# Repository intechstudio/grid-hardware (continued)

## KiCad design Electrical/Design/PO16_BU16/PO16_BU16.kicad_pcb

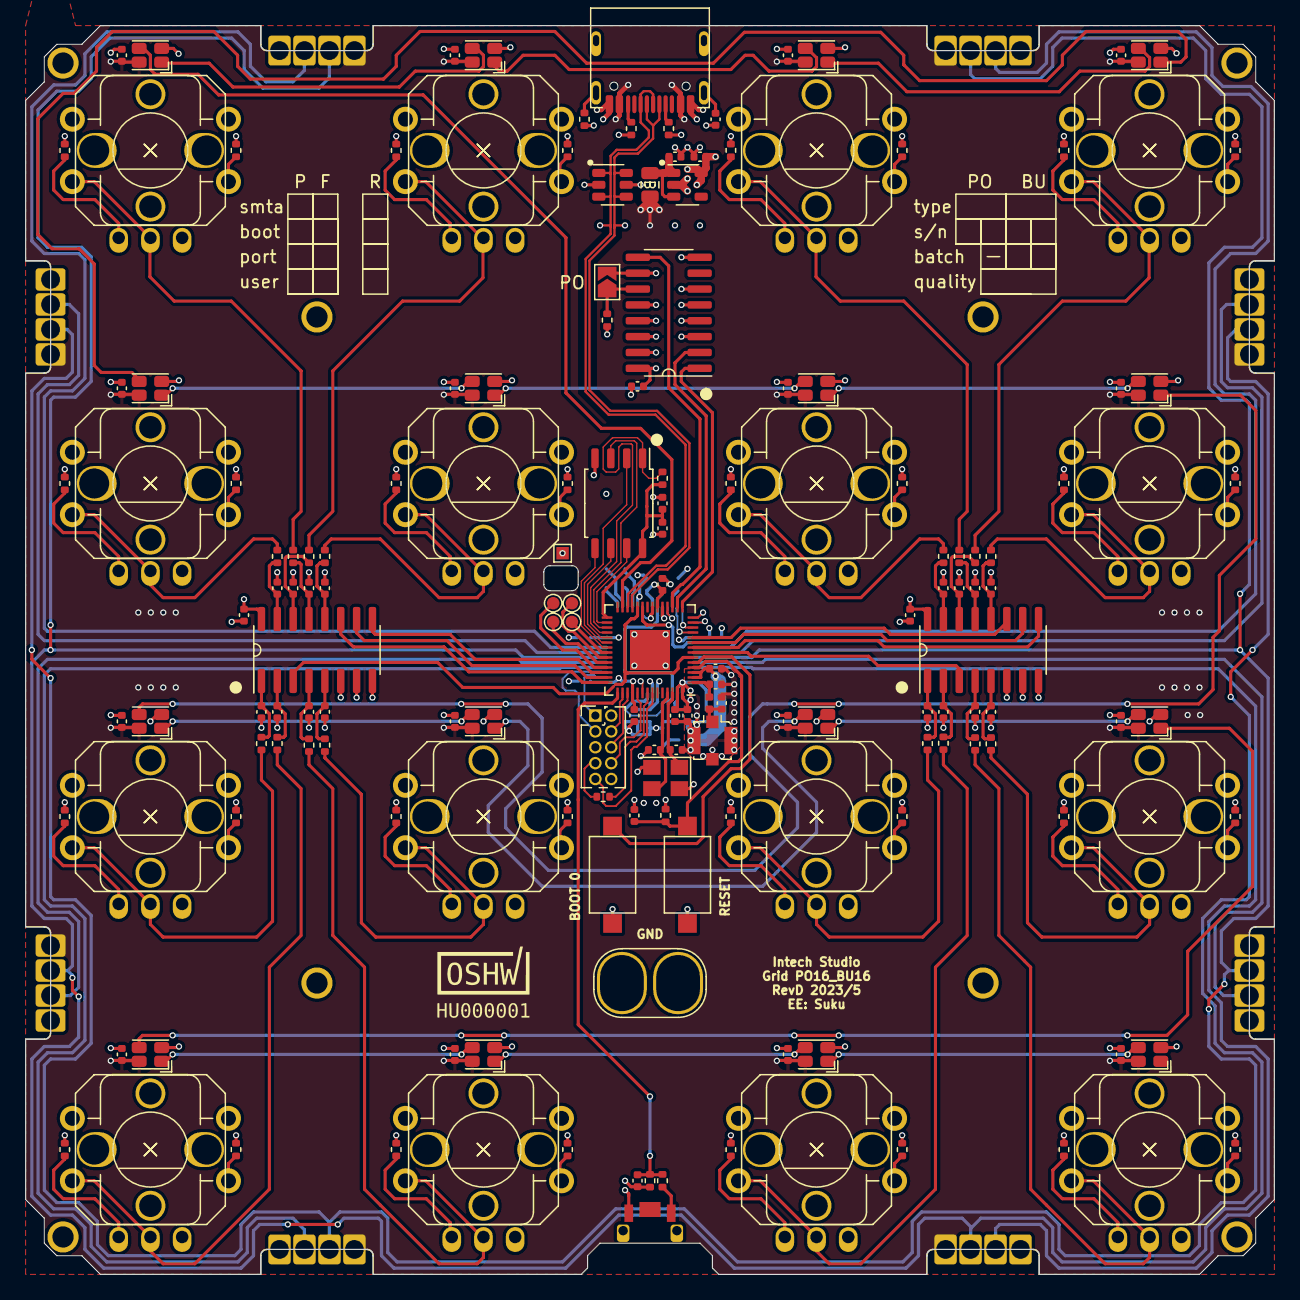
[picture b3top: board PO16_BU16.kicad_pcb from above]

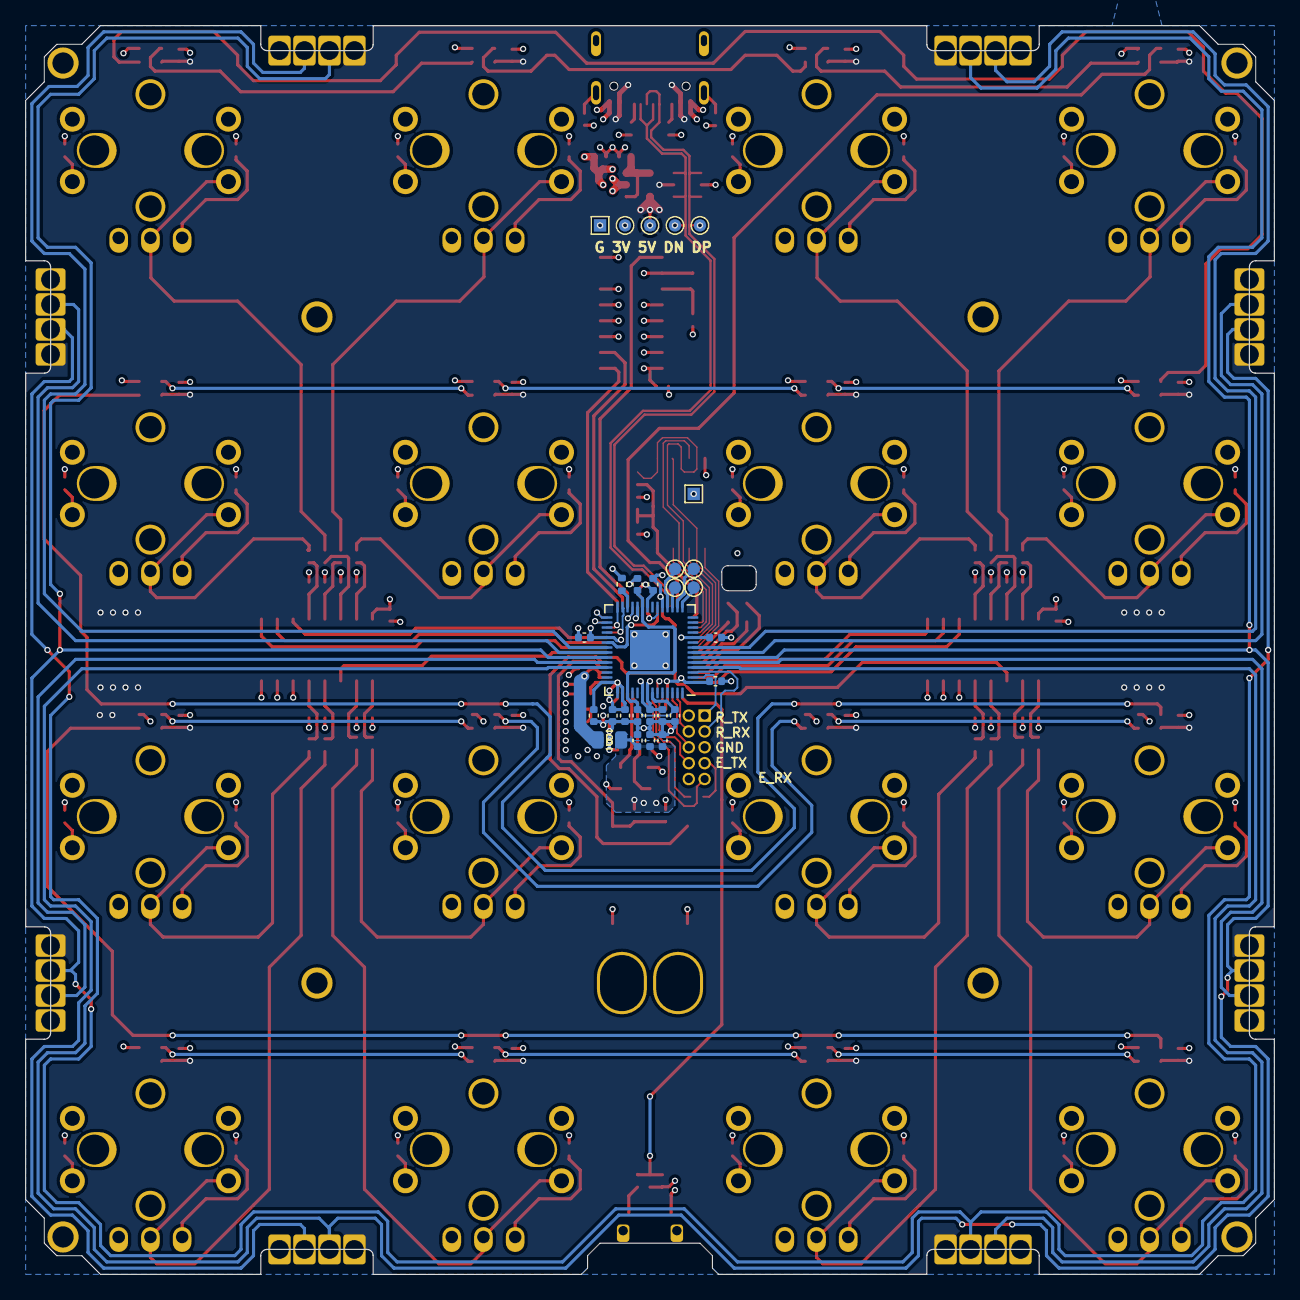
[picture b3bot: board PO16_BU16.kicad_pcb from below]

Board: 4 copper layers, 100.0 x 100.0 mm, 217 parts (28 on the bottom side), 155 nets.

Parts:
C731, C732, C735, C736, C737, C738, C740, C741, C744, C745, C747, C749, C751, C752, C756, C757, C801, C901, C902, C903, C904, C905, C906, C907, C908, C909, C910, C911, C912, C913, C914, C915, C916, C1001, C1002, C1003, C1004, C1005, C1006, C1007, C1008, C1009, C1010, C1011, C1012, C1013, C1014, C1015, C1016, C1017, C1018: 100n; CAP_0402
C733, C734, C746, C754, C755, C758, C760, C761: 1u; CAP_0402
C739: 3p9; CAP_0402
C742: 1p8; CAP_0402
C743: 10u; CAP_0402
C748, C750: 10p; CAP_0402
C753: 10n; CAP_0402
C759: 4n7; CAP_0402
D901, D902, D903, D904, D905, D906, D907, D908, D909, D910, D911, D912, D913, D914, D915, D916: WS2812C-2020; UI_WS2812C-2020
J701: Conn_Coaxial; U.FL_Molex_MCRF_73412-0110_Vertical
J702: (NF); PinHeader_2x05_P1.27mm_Vertical
J703, J704, J705, J706, J707, J708, J709, J710: AFB10-S08LCA-00; J_INTERFACE_SPRINGPATTERN
J711: USB_C_TYPE-C-32-M-12; USB_C_Korean_Hroparts_TYPE-C-31-M-12
J799: Conn_01x02; OscilloscopeGround
JP801: (NF); SolderJumper-2_P1.3mm_Open_TrianglePad1.0x1.5mm
L701: 1n8; IND_0402
L702, L703: GZ2012D601TF; FERRIT_0805
LOGO701: LOGO; OSHWA
M701: (NF); grid_outline
R701, R729, R734, R735, R738, R739, R801, R1033, R1034, R1035, R1036, R1037, R1038, R1039, R1040, R1041, R1042, R1043, R1044, R1045, R1046, R1047, R1048: 5k1; RES_0402
R733, R736, R1001, R1002, R1003, R1004, R1005, R1006, R1007, R1008, R1009, R1010, R1011, R1012, R1013, R1014, R1015, R1016: 1k; RES_0402
R737: 1M; RES_0402
R1017, R1018, R1019, R1020, R1021, R1022, R1023, R1024, R1025, R1026, R1027, R1028, R1029, R1030, R1031, R1032: 470R; RES_0402
SW701: C255807; SW_HYP_MAPMODE
SW702, SW703: C2905169; SW_SPST_CK_RS282G05A3
TP701, TP702, TP703, TP704, TP706, TP707, TP708, TP709: TestPoint; TestPoint_Pad_D1.0mm
TP705, TP710: TestPoint; TestPoint_Pad_1.0x1.0mm
TP711: GND; TestPoint_Pad_1.0x1.0mm
TP712: VB; TestPoint_Pad_D1.0mm
TP713: D-; TestPoint_Pad_D1.0mm
TP714: D+; TestPoint_Pad_D1.0mm
TP715: UI; TestPoint_Pad_D1.0mm
U703: RP2040; RP2040_QFN-56-1EP_7x7mm_P0.4mm_EP3.2x3.2mm
U704: ESP32-S3FN8; QFN-56-1EP_7x7mm_P0.4mm_EP3.2x3.2mm
U705: W25Q64JVSSIQ; SOIC-8W_FLASH
U706: SESRV05-4; SOT-23-6
U707: LN1134A332MR-G; SOT-23-5
U801: 74HC165; SOIC-16_74HC165
U1001, U1002: 74HC4051; SOIC-16_74HC4051
UI1001, UI1002, UI1003, UI1004, UI1005, UI1006, UI1007, UI1008, UI1009, UI1010, UI1011, UI1012, UI1013, UI1014, UI1015, UI1016: P090S-04F20BR10K (NF); UI_POT_TT
UI1017, UI1018, UI1019, UI1020, UI1021, UI1022, UI1023, UI1024, UI1025, UI1026, UI1027, UI1028, UI1029, UI1030, UI1031, UI1032: B3F-4050 (NF); UI_BUTTON_OMRON
Y701: ESP32_XTAL; Crystal_SMD_Abracon_ABM8G-4Pin_3.2x2.5mm

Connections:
+1V1: C731.1, C732.1, C733.1, U703.23 (DVDD), U703.45 (VREG_VOUT), U703.50 (DVDD)
+3V3: C734.1, C735.1, C736.1, C737.1, C738.1, C740.1, C741.1, C743.1, C744.1, C745.1, C746.1, C747.1, C751.1, C752.1, C753.1, C754.1, C757.2, C761.2, C801.1, C1009.1, C1018.1, L702.2, R701.1, R729.1, R735.1, R801.1, R1017.1, R1018.1, R1019.1, R1020.1, R1021.1, R1022.1, R1023.1, R1024.1, R1025.1, R1026.1, R1027.1, R1028.1, R1029.1, R1030.1, R1031.1, R1032.1, R1033.2, R1034.2, R1035.2, R1036.2, R1037.2, R1038.2, R1039.2, R1040.2, R1041.2, R1042.2, R1043.2, R1044.2, R1045.2, R1046.2, R1047.2, R1048.2, TP715.1, U703.1 (IOVDD), U703.10 (IOVDD), U703.22 (IOVDD), U703.33 (IOVDD), U703.42 (IOVDD), U703.43 (ADC_AVDD), U703.44 (VREG_IN), U703.48 (USB_VDD), U703.49 (IOVDD), U704.20 (VDD3P3_RTC), U704.46 (VDD3P3_CPU), U704.55 (VDDA1), U704.56 (VDDA2), U707.5 (OUT), U801.6 (D7), U801.16 (VCC), U1001.16 (VDD), U1002.16 (VDD)
+5V: C901.2, C902.2, C903.2, C904.2, C905.2, C906.2, C907.2, C908.2, C909.2, C910.2, C911.2, C912.2, C913.2, C914.2, C915.2, C916.2, D901.4 (VDD), D902.4 (VDD), D903.4 (VDD), D904.4 (VDD), D905.4 (VDD), D906.4 (VDD), D907.4 (VDD), D908.4 (VDD), D909.4 (VDD), D910.4 (VDD), D911.4 (VDD), D912.4 (VDD), D913.4 (VDD), D914.4 (VDD), D915.4 (VDD), D916.4 (VDD), J703.4, J704.1, J705.1, J706.4, J707.4, J708.1, J709.1, J710.4, J711.A4B9 (VBUS), J711.A9B4 (VBUS), L703.2, TP712.1, U706.5
/ANA_0: R1001.2, UI1001.2, UI1017.3
/ANA_1: R1005.2, UI1005.2, UI1021.3
/ANA_2: R1009.2, UI1009.2, UI1025.3
/ANA_3: R1013.2, UI1013.2, UI1029.3
/ANA_4: R1002.2, UI1002.2, UI1018.3
/ANA_5: R1006.2, UI1006.2, UI1022.3
/ANA_6: R1010.2, UI1010.2, UI1026.3
/ANA_7: R1014.2, UI1014.2, UI1030.3
/ANA_8: R1003.2, UI1003.2, UI1019.3
/ANA_9: R1007.2, UI1007.2, UI1023.3
/ANA_10: R1011.2, UI1011.2, UI1027.3
/ANA_11: R1015.2, UI1015.2, UI1031.3
/ANA_12: R1004.2, UI1004.2, UI1020.3
/ANA_13: R1008.2, UI1008.2, UI1024.3
/ANA_14: R1012.2, UI1012.2, UI1028.3
/ANA_15: R1016.2, UI1016.2, UI1032.3
/HWCFG/HWCFG_CLOCK: U704.16 (GPIO11), U801.2 (CLK)
/HWCFG/HWCFG_DATA: U704.17 (GPIO12), U801.9 (Q)
/HWCFG/HWCFG_SHIFT: U704.15 (GPIO10), U801.1 (SH/~LD)
/MCU/ESP_BOOT0: SW703.2 (B), U704.5 (GPIO0)
/MCU/ESP_LNA: C742.1, L701.2, U704.1 (LNA_IN)
/MCU/ESP_RESET: C758.1, R735.2, SW702.2 (B), U704.4 (CHIP_PU)
/MCU/GRID_EAST_RX: J709.3, U703.36 (GPIO24)
/MCU/GRID_EAST_TX: J710.2, U703.38 (GPIO26_ADC0)
/MCU/GRID_NORTH_RX: J705.3, U703.8 (GPIO6)
/MCU/GRID_NORTH_TX: J707.2, U703.35 (GPIO23)
/MCU/GRID_SOUTH_RX: J708.3, U703.39 (GPIO27_ADC1)
/MCU/GRID_SOUTH_TX: J706.2, U703.4 (GPIO2)
/MCU/GRID_SYNC_1: J703.3, J706.3, J707.3, J710.3, U703.37 (GPIO25)
/MCU/GRID_SYNC_2: J704.2, J705.2, J708.2, J709.2, U703.6 (GPIO4)
/MCU/GRID_WEST_RX: J704.3, U703.5 (GPIO3)
/MCU/GRID_WEST_TX: J703.2, U703.7 (GPIO5)
/MCU/LED_DATA_OUT: D901.3 (DIN), U704.27 (GPIO21)
/MCU/MAP_MODE: C757.1, R701.2, R736.2, U704.43 (GPIO38)
/MCU/RP_CLK: U703.20 (XIN), U704.21 (GPIO15)
/MCU/RP_INTERRUPT: U703.34 (GPIO22), U704.23 (GPIO17)
/MCU/RP_RUN: R729.2, U703.26 (RUN)
/MCU/RP_SPI0_CS: U703.28 (GPIO17), U704.12 (GPIO7)
/MCU/RP_SPI0_RX: U703.27 (GPIO16), U704.11 (GPIO6)
/MCU/RP_SPI0_SCK: U703.29 (GPIO18), U704.14 (GPIO9)
/MCU/RP_SPI0_TX: U703.30 (GPIO19), U704.13 (GPIO8)
/MCU/RP_SWCLK: U703.24 (SWCLK), U704.19 (GPIO14)
/MCU/RP_SWDIO: U703.25 (SWD), U704.18 (GPIO13)
/MCU/RP_UART0_RX: J702.3, U703.3 (GPIO1)
/MCU/RP_UART0_TX: J702.1, U703.2 (GPIO0)
/MCU/SPICLK: U704.33 (GPIO30), U705.6 (CLK)
/MCU/SPICS0: R734.2, U704.32 (GPIO29), U705.1 (~CS)
/MCU/SPID: U704.35 (GPIO32), U705.5 (DI(IO0))
/MCU/SPIHD: U704.30 (GPIO27), U705.7 (IO3)
/MCU/SPIQ: U704.34 (GPIO31), U705.2 (DO(IO1))
/MCU/SPIWP: U704.31 (GPIO28), U705.3 (IO2)
/MCU/TCK: J702.4, U704.44 (GPIO39)
/MCU/TDI: J702.8, U704.47 (GPIO41)
/MCU/TDO: J702.6, U704.45 (GPIO40)
/MCU/TMS: J702.2, U704.48 (GPIO42)
/MCU/U0RXD: J702.9, U704.50 (GPIO44)
/MCU/U0TXD: R733.2, U704.49 (GPIO43)
/MCU/USB_DN: J711.A7 (D-), J711.B7 (D-), TP713.1, U704.25 (GPIO19), U706.4, U706.6
/MCU/USB_DP: J711.A6 (D+), J711.B6 (D+), TP714.1, U704.26 (GPIO20), U706.1, U706.3
ESP_GPIO_1: U704.6 (GPIO1), U704.24 (GPIO18), U1001.3 (X)
ESP_GPIO_2: U704.7 (GPIO2), U1002.3 (X)
ESP_GPIO_3: U704.8 (GPIO3), U1002.9 (C)
ESP_GPIO_4: U704.9 (GPIO4), U1002.10 (B)
ESP_GPIO_5: U704.10 (GPIO5), U1002.11 (A)
ESP_GPIO_33: TP709.1, U704.38 (GPIO33)
ESP_GPIO_34: TP708.1, U704.39 (GPIO34)
ESP_GPIO_35: U704.40 (GPIO35), U1001.9 (C)
ESP_GPIO_36: U704.41 (GPIO36), U1001.10 (B)
ESP_GPIO_37: U704.42 (GPIO37), U1001.11 (A)
ESP_GPIO_47: TP706.1, U704.37 (GPIO47)
ESP_GPIO_48: TP707.1, U704.36 (GPIO48)
GND: C731.2, C732.2, C733.2, C734.2, C735.2, C736.2, C737.2, C738.2, C739.2, C740.2, C741.2, C742.2, C743.2, C744.2, C745.2, C746.2, C747.2, C748.2, C749.2, C750.2, C751.2, C752.2, C753.2, C754.2, C755.2, C756.2, C758.2, C759.2, C760.2, C761.1, C801.2, C901.1, C902.1, C903.1, C904.1, C905.1, C906.1, C907.1, C908.1, C909.1, C910.1, C911.1, C912.1, C913.1, C914.1, C915.1, C916.1, C1001.2, C1002.2, C1003.2, C1004.2, C1005.2, C1006.2, C1007.2, C1008.2, C1009.2, C1010.2, C1011.2, C1012.2, C1013.2, C1014.2, C1015.2, C1016.2, C1017.2, C1018.2, D901.2 (VSS), D902.2 (VSS), D903.2 (VSS), D904.2 (VSS), D905.2 (VSS), D906.2 (VSS), D907.2 (VSS), D908.2 (VSS), D909.2 (VSS), D910.2 (VSS), D911.2 (VSS), D912.2 (VSS), D913.2 (VSS), D914.2 (VSS), D915.2 (VSS), D916.2 (VSS), J701.2 (Ext), J702.5, J703.1, J704.4, J705.4, J706.1, J707.1, J708.4, J709.4, J710.1, J711.A1B12 (GND), J711.A12B1 (GND), J799.1, J799.2, JP801.2 (B), R737.2, R738.2, R739.2, SW701.2 (B), SW702.1 (A), SW703.1 (A), TP705.1, TP710.1, TP711.1, U703.19 (TESTEN), U703.57 (GND), U704.57 (GND), U705.4 (GND), U706.2, U707.2 (GND), U801.3 (D4), U801.4 (D5), U801.5 (D6), U801.8 (GND), U801.10 (SI), U801.12 (D1), U801.13 (D2), U801.14 (D3), U801.15 (INH), U1001.6 (Inh), U1001.7 (VEE), U1001.8 (VSS), U1002.6 (Inh), U1002.7 (VEE), U1002.8 (VSS), UI1001.3, UI1002.3, UI1003.3, UI1004.3, UI1005.3, UI1006.3, UI1007.3, UI1008.3, UI1009.3, UI1010.3, UI1011.3, UI1012.3, UI1013.3, UI1014.3, UI1015.3, UI1016.3, UI1017.1, UI1017.2, UI1018.1, UI1018.2, UI1019.1, UI1019.2, UI1020.1, UI1020.2, UI1021.1, UI1021.2, UI1022.1, UI1022.2, UI1023.1, UI1023.2, UI1024.1, UI1024.2, UI1025.1, UI1025.2, UI1026.1, UI1026.2, UI1027.1, UI1027.2, UI1028.1, UI1028.2, UI1029.1, UI1029.2, UI1030.1, UI1030.2, UI1031.1, UI1031.2, UI1032.1, UI1032.2, Y701.2, Y701.4
unnamed: C749.1, L702.1, U704.2 (VDD3P3), U704.3 (VDD3P3)
unnamed: C760.1, L703.1, U707.1 (IN), U707.3 (EN)
unnamed: C759.1, J711.S1 (SHIELD)
unnamed: D901.1 (DOUT), D905.3 (DIN)
unnamed: D902.3 (DIN), D913.1 (DOUT)
unnamed: D902.1 (DOUT), D906.3 (DIN)
unnamed: D903.3 (DIN), D914.1 (DOUT)
unnamed: D903.1 (DOUT), D907.3 (DIN)
unnamed: D904.3 (DIN), D915.1 (DOUT)
unnamed: D904.1 (DOUT), D908.3 (DIN)
unnamed: D905.1 (DOUT), D909.3 (DIN)
unnamed: D906.1 (DOUT), D910.3 (DIN)
unnamed: D907.1 (DOUT), D911.3 (DIN)
unnamed: D908.1 (DOUT), D912.3 (DIN)
unnamed: D909.1 (DOUT), D913.3 (DIN)
unnamed: D910.1 (DOUT), D914.3 (DIN)
unnamed: D911.1 (DOUT), D915.3 (DIN)
unnamed: D912.1 (DOUT), D916.3 (DIN)
unnamed: C739.1, J701.1 (In), L701.1
unnamed: J702.7, R733.1
unnamed: J711.A5 (CC1), R738.1
unnamed: J711.B5 (CC2), R739.1
unnamed: J711.S2 (SHIELD), R737.1
unnamed: JP801.1 (A), R801.2, U801.11 (D0)
unnamed: R1017.2, UI1001.1
unnamed: R1018.2, UI1002.1
unnamed: R1019.2, UI1003.1
unnamed: R1020.2, UI1004.1
unnamed: R1021.2, UI1005.1
unnamed: R1022.2, UI1006.1
unnamed: R1023.2, UI1007.1
unnamed: R1024.2, UI1008.1
unnamed: R1025.2, UI1009.1
unnamed: R1026.2, UI1010.1
unnamed: R1027.2, UI1011.1
unnamed: R1028.2, UI1012.1
unnamed: R1029.2, UI1013.1
unnamed: R1030.2, UI1014.1
unnamed: R1031.2, UI1015.1
unnamed: R1032.2, UI1016.1
unnamed: R1033.1, UI1017.4
unnamed: R1034.1, UI1018.4
unnamed: R1035.1, UI1019.4
unnamed: R1036.1, UI1020.4
unnamed: R1037.1, UI1021.4
unnamed: R1038.1, UI1022.4
unnamed: R1039.1, UI1023.4
unnamed: R1040.1, UI1024.4
unnamed: R1041.1, UI1025.4
unnamed: R1042.1, UI1026.4
unnamed: R1043.1, UI1027.4
unnamed: R1044.1, UI1028.4
unnamed: R1045.1, UI1029.4
unnamed: R1046.1, UI1030.4
unnamed: R1047.1, UI1031.4
unnamed: R1048.1, UI1032.4
unnamed: R736.1, SW701.1 (A)
unnamed: TP701.1, U703.15 (GPIO12)
unnamed: TP702.1, U703.16 (GPIO13)
unnamed: TP703.1, U703.17 (GPIO14)
unnamed: TP704.1, U703.18 (GPIO15)
unnamed: C750.1, U704.53 (XTAL_N), Y701.3
unnamed: C748.1, U704.54 (XTAL_P), Y701.1
unnamed: C1001.1, R1001.1, U1001.13 (X0)
unnamed: C1005.1, R1005.1, U1001.14 (X1)
unnamed: C1002.1, R1002.1, U1001.15 (X2)
unnamed: C1006.1, R1006.1, U1001.12 (X3)
unnamed: C1003.1, R1003.1, U1001.1 (X4)
unnamed: C1007.1, R1007.1, U1001.5 (X5)
unnamed: C1004.1, R1004.1, U1001.2 (X6)
unnamed: C1008.1, R1008.1, U1001.4 (X7)
unnamed: C1010.1, R1009.1, U1002.13 (X0)
unnamed: C1014.1, R1013.1, U1002.14 (X1)
unnamed: C1011.1, R1010.1, U1002.15 (X2)
unnamed: C1015.1, R1014.1, U1002.12 (X3)
unnamed: C1012.1, R1011.1, U1002.1 (X4)
unnamed: C1016.1, R1015.1, U1002.5 (X5)
unnamed: C1013.1, R1012.1, U1002.2 (X6)
unnamed: C1017.1, R1016.1, U1002.4 (X7)
VDD_SPI: C755.1, C756.1, R734.1, U704.29 (VDD_SPI), U705.8 (VCC)
